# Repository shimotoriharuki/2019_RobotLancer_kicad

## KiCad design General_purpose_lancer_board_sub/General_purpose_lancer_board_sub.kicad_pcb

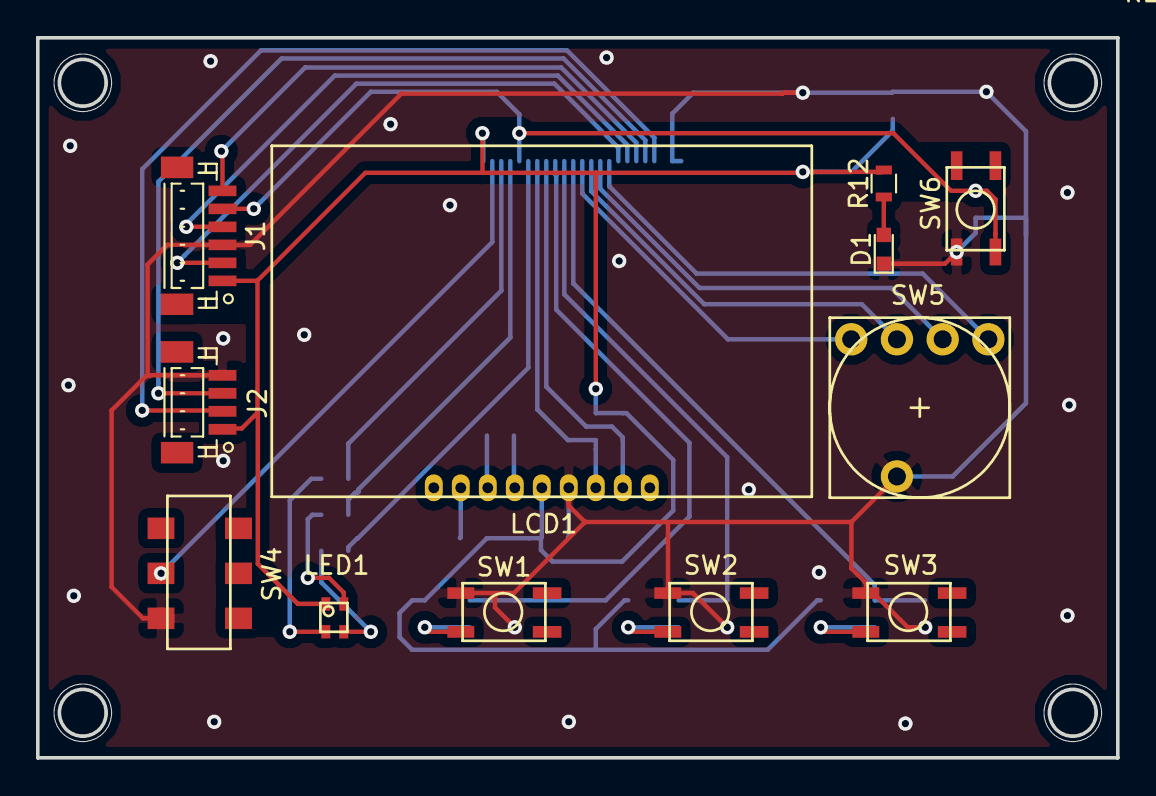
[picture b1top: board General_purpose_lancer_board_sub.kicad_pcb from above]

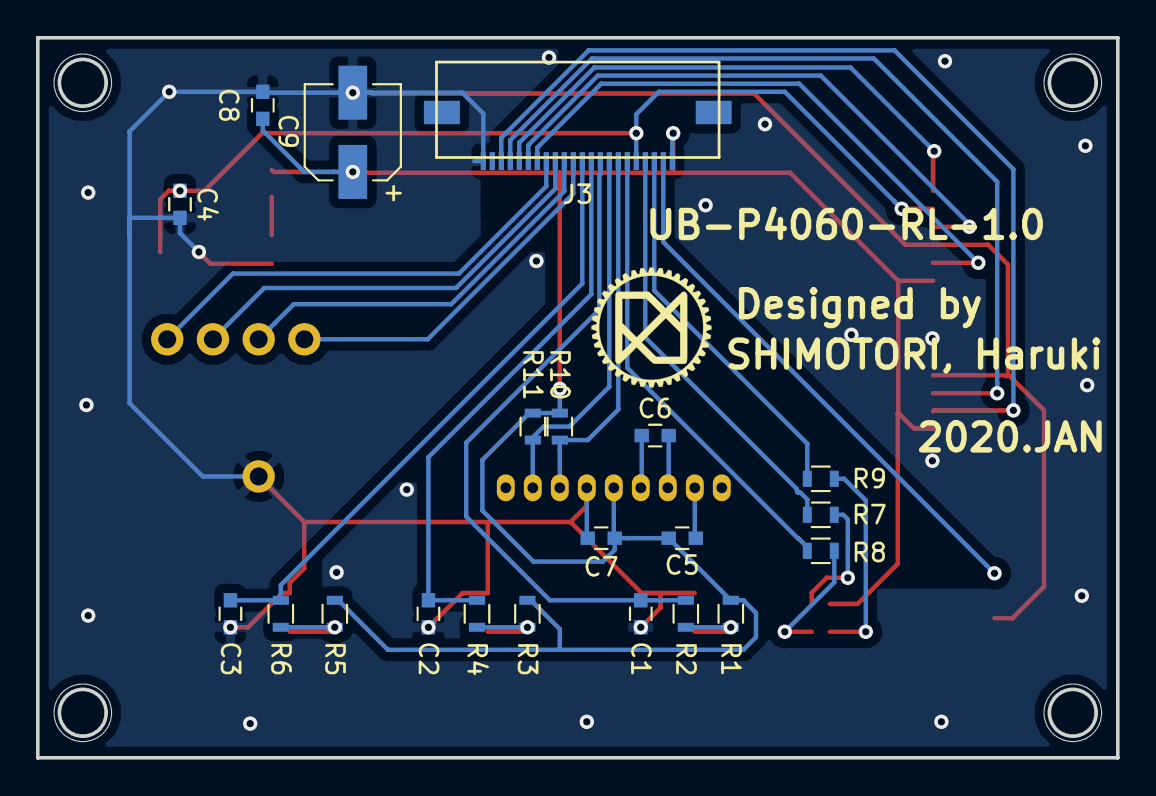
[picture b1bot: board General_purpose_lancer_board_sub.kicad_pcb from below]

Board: 2 copper layers, 60.0 x 40.0 mm, 33 parts (21 on the bottom side), 31 nets.

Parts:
C1, C2, C3, C4, C7: 0.1u; C_0603
C5, C6: 1u; C_0603
C8: 0.1; C_0603
C9: 82u; CP_Elec_5x5.8
D1: LED; LED_0603
J1: SH; JST_SH_BM06B-SRSS-TB_06x1.00mm_Straight
J2: SH; JST_SH_BM04B-SRSS-TB_04x1.00mm_Straight
J3: FFC; Molex_FFC_22
LCD1: AQM0802A
LED1: OSTB0603C1C-A
R1, R2, R3, R4, R5, R6: 10k; R_0603
R7: 1.2k; R_0603
R8: 680; R_0603
R9: 470; R_0603
R10, R11: 4.7k; R_0603
R12: 360; R_0603
SW1, SW2, SW3, SW6: SKRPACE010
SW4: SSSS213202
SW5: FR01SC16P-S; FR01SC16P

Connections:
+3V3: C5.2, C7.2, C8.1, C9.1, J1.1, J2.1, J3.22, LCD1.5, LED1.1, R1.1, R3.1, R5.1, R10.1, R11.1, R12.1
GND: C1.1, C2.1, C3.1, C4.2, C7.1, C8.2, C9.2, D1.1, J1.3, J2.4, J3.1, LCD1.6, SW1.2, SW2.2, SW3.2, SW4.3, SW5.C, SW6.2
I2C_SCL_LCD: J3.15, LCD1.8, R11.2
I2C_SDA_LCD: J3.16, LCD1.7, R10.2
LED2_B: J3.20, R9.1
LED2_G: J3.17, R8.1
LED2_R: J3.19, R7.1
NRST: C4.1, J1.5, J3.18, SW6.1
unnamed: C5.1, LCD1.2
unnamed: C6.1, LCD1.4
unnamed: C6.2, LCD1.3
unnamed: D1.2, R12.2
unnamed: LED1.2, R7.2
unnamed: LED1.3, R9.2
unnamed: LED1.4, R8.2
unnamed: R1.2, R2.2, SW1.1
unnamed: R3.2, R4.2, SW2.1
unnamed: R5.2, R6.2, SW3.1
POWER_SW: J3.21, SW4.2
R_SW1: J3.11, SW5.1
R_SW2: J3.10, SW5.2
R_SW4: J3.9, SW5.4
R_SW8: J3.8, SW5.8
SWCLK: J1.2, J3.7
SWDIO: J1.4, J3.6
SWO: J1.6, J3.5
T_SW1: C1.2, J3.14, R2.1
T_SW2: C2.2, J3.13, R4.1
T_SW3: C3.2, J3.12, R6.1
UART_RX: J2.2, J3.3
UART_TX: J2.3, J3.4

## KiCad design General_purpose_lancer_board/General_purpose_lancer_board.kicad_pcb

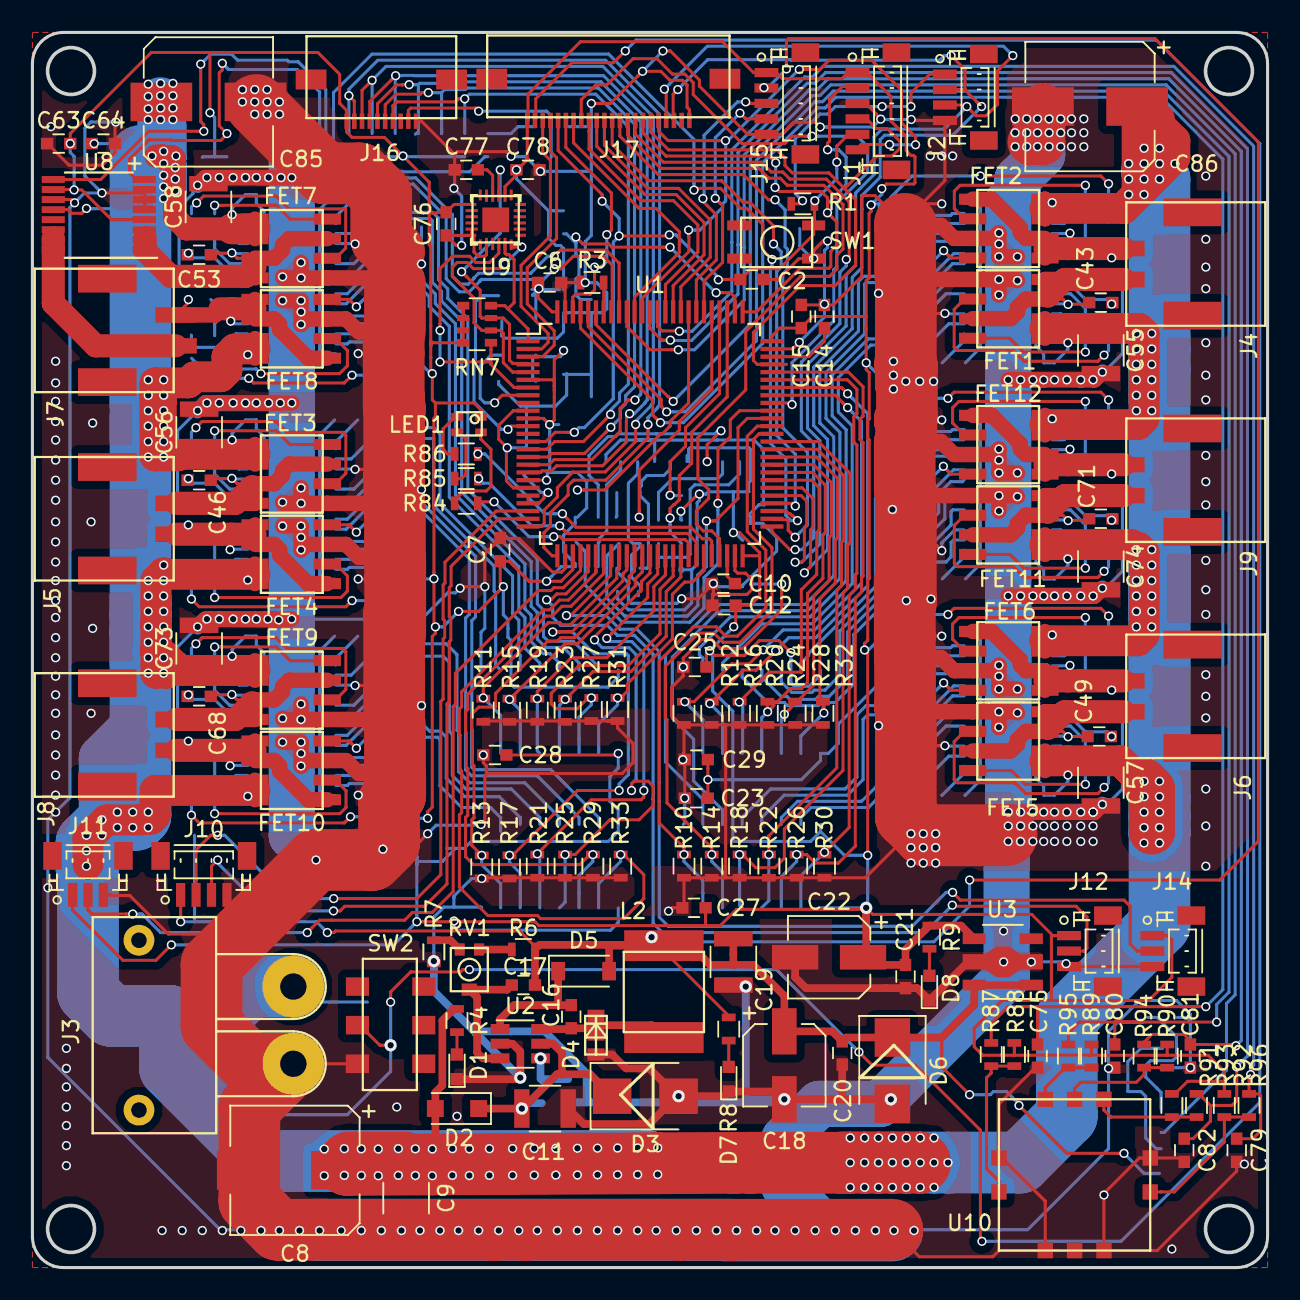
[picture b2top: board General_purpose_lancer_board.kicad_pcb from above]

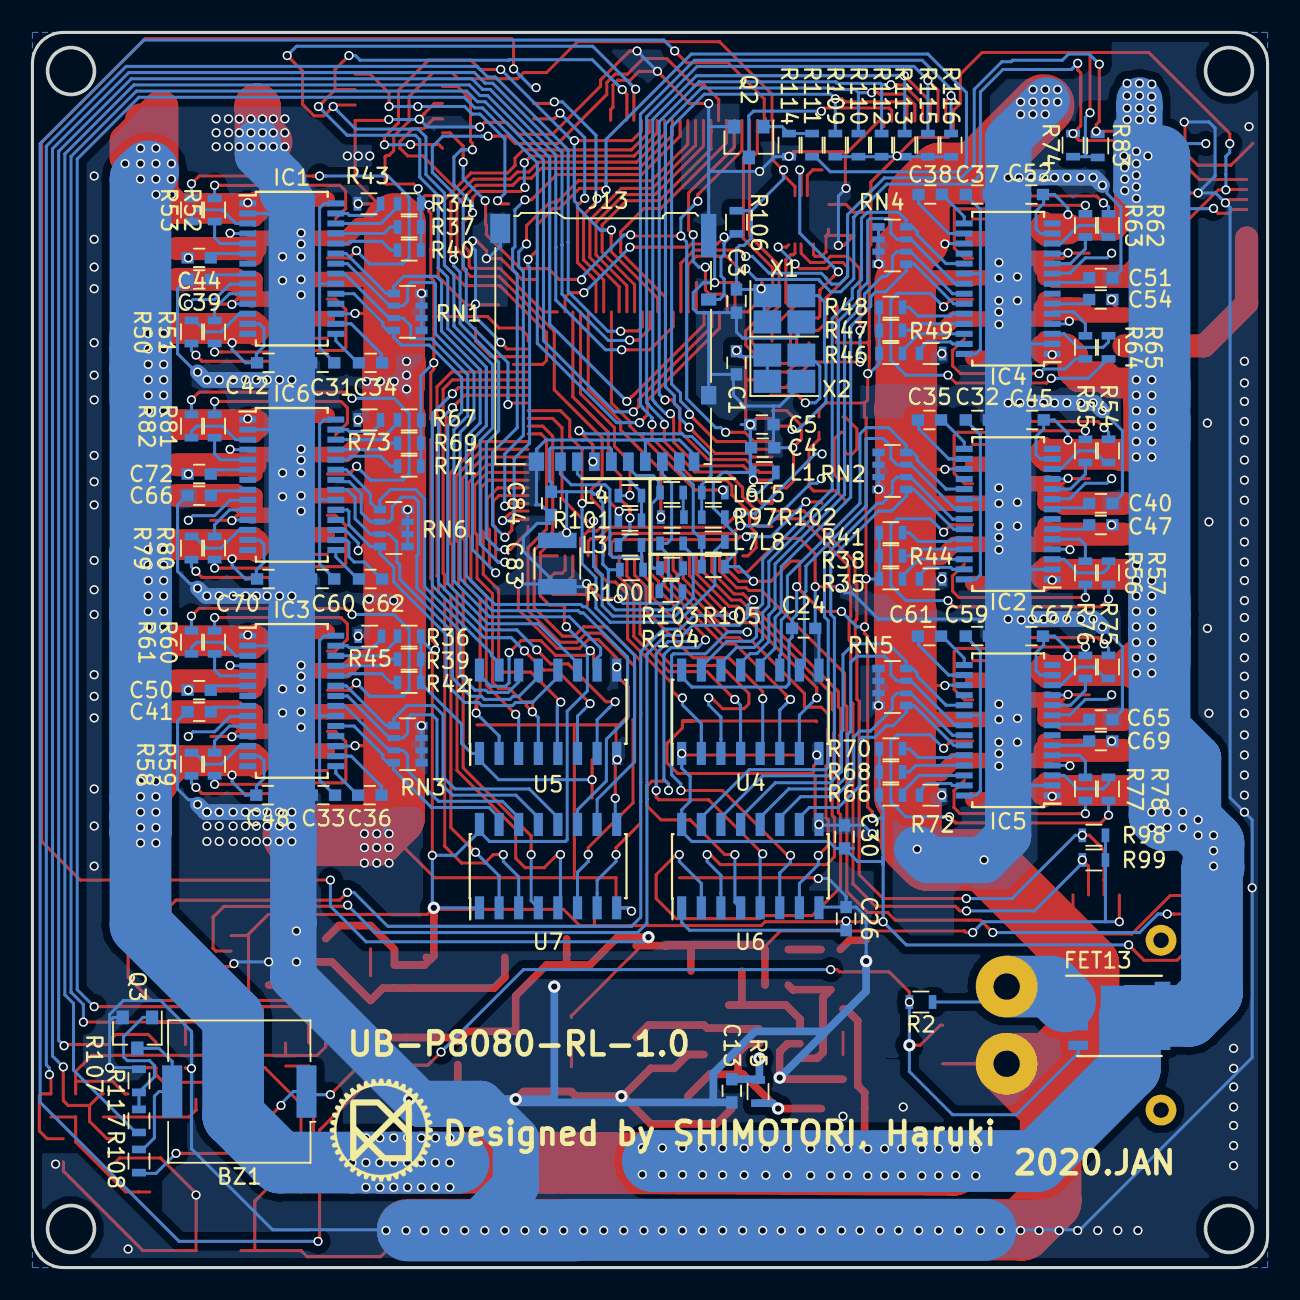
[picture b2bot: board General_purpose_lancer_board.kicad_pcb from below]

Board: 2 copper layers, 80.0 x 80.0 mm, 281 parts (143 on the bottom side), 265 nets.

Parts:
BZ1: PKMCS0909E4000-R1; Buzzer_Murata_PKMCS0909E4000-R1
C1, C2, C3, C4, C5, C6, C7, C12, C13, C15, C23, C24, C25, C26, C27, C28, C29, C30, C31, C32, C33, C37, C59, C60, C63, C64, C76, C77, C78: 0.1u; C_0603
C8, C85, C86: 330u; CP_Elec_8x6.7
C9, C11, C19, C55, C56, C57, C58, C73, C74, C83: 47u; C_1210
C10, C14: 2.2u; C_0603
C16: 0.01u; C_0603
C17: 470p; C_0603
C18, C22: 100u; CP_Elec_5x5.8
C20: 1u; C_0603
C21, C42, C45, C48, C52, C67, C70, C75, C79, C80, C81, C82: 10u; C_0603
C34, C35, C36, C38, C61, C62: 470n; C_0603
C39, C40, C41, C43, C44, C46, C47, C49, C50, C51, C53, C54, C65, C66, C68, C69, C71, C72: 0.22u; C_0603
C84: 0.1; C_0603
D1, D7, D8: OSBL1608; LED_0603
D2: SS2040; D_SOD-123F
D3: 1SMB5930BT3G; D_SMB
D4: RSX101VAM; TUMD2M
D5: 1N4148; D_SOD-123
D6: 1SMB5920BT3G; D_SMB
FET1, FET2, FET3, FET4, FET5, FET6, FET7, FET8, FET9, FET10, FET11, FET12: IRF8915
FET13: SiSS27ADN; SO-8_PowerPAK_Vishay_Single
IC1, IC2, IC3, IC4, IC5, IC6: A3921; TSSOP-28-1EP_4.4x9.7mm_Pitch0.65mm
J1: SH; JST_SH_BM06B-SRSS-TB_06x1.00mm_Straight
J2, J10: SH; JST_SH_BM04B-SRSS-TB_04x1.00mm_Straight
J3: XT30; XT30PW-M
J4, J5, J6, J7, J8, J9: PA_SIDE; SM02B-PASS
J11, J12, J14: SH; JST_SH_BM03B-SRSS-TB_03x1.00mm_Straight
J13: Micro_SD_Card_Det_Hirose_DM3AT; Hirose_DM3AT-SF-PEJM5
J15: SH; JST_SH_BM05B-SRSS-TB_05x1.00mm_Straight
J16: FFC; Molex_FFC_10
J17: FFC; Molex_FFC_22
L1: 330; L_0603
L2: 22u; SD25-220-R
L3, L4, L5, L6, L7, L8: 100; L_0603
LED1: OSTB0603C1C-A
Q2: IRLML6344; SOT-23
Q3: BSS138; SOT-23
R1: 50k; R_0603
R2: 12k; R_0603
R3, R7, R87, R88, R89, R90, R91, R92, R93, R94, R95, R96, R98, R99, R107: 10k; R_0603
R4: 6.8K; R_0603
R5: 15K; R_0603
R6: 30k; R_0603
R8: 1.8K; R_0603
R9: 390; R_0603
R10, R11, R12, R13, R14, R15, R16, R17, R18, R19, R20, R21, R22, R23, R24, R25, R26, R27, R28, R29, R30, R31, R32, R33, R34, R35, R36, R37, R38, R39, R40, R41, R42, R46, R47, R48, R66, R67, R68, R69, R70, R71: 10K; R_0603
R43, R44, R45, R49, R72, R73: 5k; R_0603
R50, R51, R52, R53, R54, R55, R56, R57, R58, R59, R60, R61, R62, R63, R64, R65, R75, R76, R77, R78, R79, R80, R81, R82: 75; R_0603
R74, R83: 4.7k; R_0603
R84: 1.2k; R_0603
R85: 680; R_0603
R86: 470; R_0603
R97: 0; R_0603
R100, R101, R102, R103, R104, R105, R106: 22k; R_0603
R108: 1k; R_0603
R109, R110, R112, R113, R115, R116: R; R_0603
R111, R117: 45; R_0603
R114: 47k; R_0603
RN1, RN2, RN3, RN4, RN5, RN6: 10K; R_Array_Convex_4x0603
RN7: 4.7k; R_Array_Convex_4x0603
RV1: ST2TA101; ST2TA
SW1: SW_Push; SKRPACE010
SW2: SSSS213202
U1: STM32F446VE; LQFP-100_14x14mm_Pitch0.5mm
U2: LT1933; TSOT-23-6
U3: NJM2884U1-33; SOT-89-5_Housing
U4, U5, U6, U7: SI8660BA; SOIC-16_3.9x9.9mm_Pitch1.27mm
U8: INA260; TSSOP-16_4.4x5mm_Pitch0.65mm
U9: ICM20648
U10: JS1300AQ; JS1300
X1: ECS-2520S; Crystal_SMD_EuroQuartz_X22-4pin_2.5x2.0mm_HandSoldering
X2: TC25L5I32K7680; Crystal_SMD_EuroQuartz_X22-4pin_2.5x2.0mm_HandSoldering

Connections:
+3V3: C1.1, C3.1, C4.2, C5.1, C6.2, C7.1, C12.1, C15.1, C21.1, C22.1, C23.1, C24.1, C25.1, C26.1, C27.1, C28.1, C29.1, C30.1, C63.1, C76.1, C78.2, C83.1, C84.1, J1.1, J2.1, J11.1, J12.1, J13.4, J14.1, J15.1, J16.1, J17.1, L1.2, LED1.1, R1.1, R9.1, R34.1, R35.1, R36.1, R37.1, R38.1, R39.1, R40.1, R41.1, R42.1, R46.1, R47.1, R48.1, R66.1, R67.1, R68.1, R69.1, R70.1, R71.1, R74.1, R83.1, R88.1, R89.1, R90.1, R91.1, R92.1, R100.1, R101.1, R102.1, R104.1, R105.1, R106.1, R109.1, R110.1, R112.1, R113.1, R115.1, R116.1, RN7.5, RN7.6, RN7.7, RN7.8, U1.6, U1.11, U1.19, U1.28, U1.50, U1.75, U1.100, U3.4, U4.1, U4.16, U5.1, U5.16, U6.1, U6.16, U7.1, U7.16, U8.4, U8.10, U9.8, U9.13, X1.1, X1.4, X2.1, X2.4
+5V: BZ1.1, C17.1, C18.1, C19.1, C20.1, D5.2, D6.1, J10.1, J15.2, L2.1, R6.1, R8.1, R98.1, R99.1, R108.2, U3.1, U3.5
+BATT: C8.1, C9.1, C42.1, C45.1, C48.1, C52.1, C55.1, C56.1, C57.1, C58.1, C64.1, C67.1, C70.1, C73.1, C74.1, C85.1, C86.1, D2.2, FET1.5, FET1.6, FET2.7, FET2.8, FET3.5, FET3.6, FET4.7, FET4.8, FET5.5, FET5.6, FET6.7, FET6.8, FET7.5, FET7.6, FET8.7, FET8.8, FET9.5, FET9.6, FET10.7, FET10.8, FET11.5, FET11.6, FET12.7, FET12.8, FET13.5, FET13.6, FET13.7, FET13.8, IC1.1, IC1.13, IC2.1, IC2.13, IC3.1, IC3.13, IC4.1, IC4.13, IC5.1, IC5.13, IC6.1, IC6.13, R4.1, U8.12
ADC_LINE1: J16.7, R109.2, U1.15
ADC_LINE2: J16.6, R110.2, U1.16
ADC_LINE3: J16.5, R112.2, U1.17
ADC_LINE4: J16.4, R113.2, U1.18
ADC_LINE5: J16.3, R115.2, U1.25
ADC_LINE6: J16.2, R116.2, U1.26
ADC_POT1: J11.2, U1.29
ADC_POT2: J12.2, U1.30
ADC_POT3: J14.2, U1.33
C_SW1: C82.1, R93.1, U1.88
C_SW2: C81.1, R94.1, U1.91
C_SW3: C80.1, R95.1, U1.96
C_SW4: C79.1, R96.1, U1.87
C_SW5: C75.1, R87.2, U1.97
ENCORDER_A: J10.2, R98.2, U1.23
ENCORDER_B: J10.3, R99.2, U1.24
GND: C1.2, C2.2, C3.2, C4.1, C5.2, C6.1, C7.2, C8.2, C9.2, C10.2, C11.2, C12.2, C13.2, C14.1, C15.2, C18.2, C19.2, C20.2, C21.2, C22.2, C23.2, C24.2, C25.2, C26.2, C27.2, C28.2, C29.2, C30.2, C31.2, C32.2, C33.2, C37.2, C39.2, C40.2, C41.2, C42.2, C45.2, C48.2, C51.2, C52.2, C55.2, C56.2, C57.2, C58.2, C59.2, C60.2, C63.2, C64.2, C65.2, C66.2, C67.2, C70.2, C73.2, C74.2, C75.2, C76.2, C77.1, C78.1, C79.2, C80.2, C81.2, C82.2, C83.2, C84.2, C85.2, C86.2, D1.1, D3.2, D4.2, D6.2, D7.1, D8.1, FET1.1, FET2.3, FET3.1, FET4.3, FET5.1, FET6.3, FET7.1, FET8.3, FET9.1, FET10.3, FET11.1, FET12.3, IC1.2, IC1.17, IC1.29, IC2.2, IC2.17, IC2.29, IC3.2, IC3.17, IC3.29, IC4.2, IC4.17, IC4.29, IC5.2, IC5.17, IC5.29, IC6.2, IC6.17, IC6.29, J1.3, J2.4, J3.2, J10.4, J11.3, J12.3, J13.6, J13.9, J13.11, J14.3, J15.5, J16.10, J17.22, Q2.2, Q3.2, R3.1, R7.2, R10.2, R11.2, R12.2, R13.2, R14.2, R15.2, R16.2, R17.2, R18.2, R19.2, R20.2, R21.2, R22.2, R23.2, R24.2, R25.2, R26.2, R27.2, R28.2, R29.2, R30.2, R31.2, R32.2, R33.2, R43.2, R44.2, R45.2, R49.2, R72.2, R73.2, R103.2, R107.2, R114.2, RN1.1, RN1.2, RN1.3, RN1.4, RN2.1, RN2.2, RN2.3, RN2.4, RN3.1, RN3.2, RN3.3, RN3.4, RN4.1, RN4.2, RN4.3, RN4.4, RN5.1, RN5.2, RN5.3, RN5.4, RN6.1, RN6.2, RN6.3, RN6.4, SW1.2, SW2.3, U1.10, U1.20, U1.27, U1.49, U1.74, U1.99, U2.2, U3.2, U4.8, U4.9, U5.8, U5.9, U6.8, U6.9, U7.8, U7.9, U8.5, U8.6, U8.7, U8.11, U9.17, U9.18, U9.20, U10.1, U10.3, U10.4, U10.5, U10.7, X1.2, X2.2
GPIO_DRIVE1_P: R15.1, U1.37, U4.6
GPIO_DRIVE1_P_I: IC2.19, RN2.8, U4.11
GPIO_DRIVE1_SR: R11.1, U1.34, U4.7
GPIO_DRIVE1_SR_I: IC2.21, RN2.7, U4.10
GPIO_DRIVE2_P: R25.1, U1.38, U6.4
GPIO_DRIVE2_P_I: IC5.19, RN5.8, U6.13
GPIO_DRIVE2_SR: R21.1, U1.39, U6.5
GPIO_DRIVE2_SR_I: IC5.21, RN5.7, U6.12
GPIO_DRIVE3_P: R20.1, U1.57, U5.5
GPIO_DRIVE3_P_I: IC6.19, RN6.8, U5.12
GPIO_DRIVE3_SR: R24.1, U1.58, U5.4
GPIO_DRIVE3_SR_I: IC6.21, RN6.7, U5.13
GPIO_DRIVE4_P: R30.1, U1.70, U7.2
GPIO_DRIVE4_P_I: IC3.19, RN3.8, U7.15
GPIO_DRIVE4_SR: R26.1, U1.71, U7.3
GPIO_DRIVE4_SR_I: IC3.21, RN3.7, U7.14
GPIO_SERVO1_SR: R27.1, U1.41, U4.3
GPIO_SERVO1_SR_I: IC4.21, RN4.7, U4.14
GPIO_SERVO2_SR: R12.1, U1.68, U5.7
GPIO_SERVO2_SR_I: IC1.21, RN1.7, U5.10
I2C_SCL_CURRENT: R83.2, U1.92, U8.9
I2C_SCL_LCD: J17.8, U1.67
I2C_SDA_CURRENT: R74.2, U1.93, U8.8
I2C_SDA_LCD: J17.7, U1.90
LED1_B: R86.1, U1.46
LED1_G: R85.1, U1.44
LED1_R: R84.1, U1.43
LED2_B: J17.3, U1.2
LED2_G: J17.6, U1.98
LED2_R: J17.4, U1.3
NRST: C2.1, J1.5, J17.5, R1.2, SW1.1, U1.14
unnamed: BZ1.2, Q3.3, R108.1
unnamed: C10.1, U1.48
unnamed: C11.1, D2.1, D3.1, R5.1, U2.5
unnamed: C13.1, R5.2, U2.4
unnamed: C14.2, U1.73
unnamed: C16.1, D5.1, U2.1
unnamed: C16.2, D4.1, L2.2, U2.6
unnamed: C17.2, RV1.2, U2.3
unnamed: C31.1, IC1.20, IC1.28
unnamed: C32.1, IC2.20, IC2.28
unnamed: C33.1, IC3.20, IC3.28
unnamed: C34.1, IC1.16
unnamed: C34.2, IC1.15
unnamed: C35.1, IC2.16
unnamed: C35.2, IC2.15
unnamed: C36.1, IC3.16
unnamed: C36.2, IC3.15
unnamed: C37.1, IC4.20, IC4.28
unnamed: C38.1, IC4.16
unnamed: C38.2, IC4.15
unnamed: C39.1, IC1.8
unnamed: C40.1, IC2.8
unnamed: C41.1, IC3.8
unnamed: C43.1, IC1.9
unnamed: C43.2, FET1.3, FET1.7, FET1.8, IC1.11, J4.1
unnamed: C44.1, IC1.6
unnamed: C44.2, FET2.1, FET2.5, FET2.6, IC1.4, J4.2
unnamed: C46.1, IC2.9
unnamed: C46.2, FET3.3, FET3.7, FET3.8, IC2.11, J5.1
unnamed: C47.1, IC2.6
unnamed: C47.2, FET4.1, FET4.5, FET4.6, IC2.4, J5.2
unnamed: C49.1, IC3.9
unnamed: C49.2, FET5.3, FET5.7, FET5.8, IC3.11, J6.1
unnamed: C50.1, IC3.6
unnamed: C50.2, FET6.1, FET6.5, FET6.6, IC3.4, J6.2
unnamed: C51.1, IC4.8
unnamed: C53.1, IC4.9
unnamed: C53.2, FET7.3, FET7.7, FET7.8, IC4.11, U8.1, U8.2, U8.3
unnamed: C54.1, IC4.6
unnamed: C54.2, FET8.1, FET8.5, FET8.6, IC4.4, J7.1
unnamed: C59.1, IC5.20, IC5.28
unnamed: C60.1, IC6.20, IC6.28
unnamed: C61.1, IC5.16
unnamed: C61.2, IC5.15
unnamed: C62.1, IC6.16
unnamed: C62.2, IC6.15
unnamed: C65.1, IC5.8
unnamed: C66.1, IC6.8
unnamed: C68.1, IC5.9
unnamed: C68.2, FET9.3, FET9.7, FET9.8, IC5.11, J8.1
unnamed: C69.1, IC5.6
unnamed: C69.2, FET10.1, FET10.5, FET10.6, IC5.4, J8.2
unnamed: C71.1, IC6.9
unnamed: C71.2, FET11.3, FET11.7, FET11.8, IC6.11, J9.1
unnamed: C72.1, IC6.6
unnamed: C72.2, FET12.1, FET12.5, FET12.6, IC6.4, J9.2
unnamed: C77.2, U9.10
unnamed: D1.2, R4.2
unnamed: D7.2, R8.2
unnamed: D8.2, R9.2
unnamed: FET1.2, R50.2
unnamed: FET1.4, R51.2
unnamed: FET2.2, R52.2
unnamed: FET2.4, R53.2
unnamed: FET3.2, R54.2
unnamed: FET3.4, R55.2
unnamed: FET4.2, R56.2
unnamed: FET4.4, R57.2
unnamed: FET5.2, R58.2
unnamed: FET5.4, R59.2
unnamed: FET6.2, R60.2
unnamed: FET6.4, R61.2
unnamed: FET7.2, R62.2
unnamed: FET7.4, R63.2
unnamed: FET8.2, R64.2
unnamed: FET8.4, R65.2
unnamed: FET9.2, R75.2
unnamed: FET9.4, R76.2
unnamed: FET10.2, R77.2
unnamed: FET10.4, R78.2
unnamed: FET11.2, R79.2
unnamed: FET11.4, R80.2
unnamed: FET12.2, R81.2
unnamed: FET12.4, R82.2
unnamed: FET13.1, FET13.2, FET13.3, J3.1, R2.1
unnamed: IC1.3, R53.1
unnamed: IC1.5, R52.1
unnamed: IC1.10, R51.1
unnamed: IC1.12, R50.1
unnamed: IC1.24, R40.2
unnamed: IC1.25, R37.2
unnamed: IC1.26, R34.2
unnamed: IC1.27, R43.1
unnamed: IC2.3, R57.1
unnamed: IC2.5, R56.1
unnamed: IC2.10, R55.1
unnamed: IC2.12, R54.1
unnamed: IC2.24, R41.2
unnamed: IC2.25, R38.2
unnamed: IC2.26, R35.2
unnamed: IC2.27, R44.1
unnamed: IC3.3, R61.1
unnamed: IC3.5, R60.1
unnamed: IC3.10, R59.1
unnamed: IC3.12, R58.1
unnamed: IC3.24, R42.2
unnamed: IC3.25, R39.2
unnamed: IC3.26, R36.2
unnamed: IC3.27, R45.1
unnamed: IC4.3, R65.1
unnamed: IC4.5, R64.1
unnamed: IC4.10, R63.1
unnamed: IC4.12, R62.1
unnamed: IC4.24, R48.2
unnamed: IC4.25, R47.2
unnamed: IC4.26, R46.2
unnamed: IC4.27, R49.1
unnamed: IC5.3, R78.1
unnamed: IC5.5, R77.1
unnamed: IC5.10, R76.1
unnamed: IC5.12, R75.1
unnamed: IC5.24, R70.2
unnamed: IC5.25, R68.2
unnamed: IC5.26, R66.2
unnamed: IC5.27, R72.1
unnamed: IC6.3, R82.1
unnamed: IC6.5, R81.1
unnamed: IC6.10, R80.1
unnamed: IC6.12, R79.1
unnamed: IC6.24, R71.2
unnamed: IC6.25, R69.2
unnamed: IC6.26, R67.2
unnamed: IC6.27, R73.1
unnamed: J7.2, U8.14, U8.15, U8.16
unnamed: J13.1, L3.1, R100.2
unnamed: J13.2, L4.1, R101.2
unnamed: J13.3, L5.1, R102.2
unnamed: J13.5, L6.1, R103.1
unnamed: J13.7, L7.1, R104.2
unnamed: J13.8, L8.1, R105.2
unnamed: J16.9, Q2.3
unnamed: L1.1, U1.21, U1.22
unnamed: L6.2, R97.1
unnamed: LED1.2, R84.2
unnamed: LED1.3, R86.2
unnamed: LED1.4, R85.2
unnamed: Q2.1, R111.1, R114.1
unnamed: Q3.1, R107.1, R117.1
unnamed: R3.2, U1.94
unnamed: R6.2, RV1.3
unnamed: R7.1, RV1.1
unnamed: R87.1, R88.2, U10.2
unnamed: R89.2, R95.2, U10.10
unnamed: R90.2, R94.2, U10.9
unnamed: R91.2, R93.2, U10.8
unnamed: R92.2, R96.2, U10.6
OSC32_IN: U1.8, X2.3
OSC_IN: U1.12, X1.3
POWER_SW: FET13.4, J17.2, R2.2, SW2.2
PWM_BZ: R117.2, U1.95
PWM_DRIVE1_H: R29.1, U1.32, U6.3
PWM_DRIVE1_H_I: IC2.23, RN2.5, U6.14
PWM_DRIVE1_L: R33.1, U1.31, U6.2
PWM_DRIVE1_L_I: IC2.22, RN2.6, U6.15
PWM_DRIVE2_H: R13.1, U1.36, U6.7
PWM_DRIVE2_H_I: IC5.23, RN5.5, U6.10
PWM_DRIVE2_L: R17.1, U1.35, U6.6
PWM_DRIVE2_L_I: IC5.22, RN5.6, U6.11
PWM_DRIVE3_H: R32.1, U1.60, U5.2
PWM_DRIVE3_H_I: IC6.23, RN6.5, U5.15
PWM_DRIVE3_L: R28.1, U1.59, U5.3
PWM_DRIVE3_L_I: IC6.22, RN6.6, U5.14
PWM_DRIVE4_H: R18.1, U1.62, U7.5
PWM_DRIVE4_H_I: IC3.23, RN3.5, U7.12
PWM_DRIVE4_L: R22.1, U1.61, U7.4
PWM_DRIVE4_L_I: IC3.22, RN3.6, U7.13
PWM_LINE_SENSOR: R111.2, U1.53
PWM_SERVO1_H: R19.1, U1.40, U4.5
PWM_SERVO1_H_I: IC4.23, RN4.5, U4.12
PWM_SERVO1_L: R23.1, U1.42, U4.4
PWM_SERVO1_L_I: IC4.22, RN4.6, U4.13
PWM_SERVO1_P: R31.1, U1.45, U4.2
PWM_SERVO1_P_I: IC4.19, RN4.8, U4.15
PWM_SERVO2_H: R10.1, U1.64, U7.7
PWM_SERVO2_H_I: IC1.23, RN1.5, U7.10
PWM_SERVO2_L: R14.1, U1.63, U7.6
PWM_SERVO2_L_I: IC1.22, RN1.6, U7.11
PWM_SERVO2_P: R16.1, U1.69, U5.6
PWM_SERVO2_P_I: IC1.19, RN1.8, U5.11
REMAINDER_PD0: J15.4, U1.81
REMAINDER_PD1: J15.3, U1.82
R_SW1: J17.12, U1.54
R_SW2: J17.13, U1.52
R_SW4: J17.14, U1.47
R_SW8: J17.15, U1.51
SDIO_CK: R97.2, U1.80
SDIO_CMD: L5.2, U1.83
SDIO_D0: L7.2, U1.65
SDIO_D1: L8.2, U1.66
SDIO_D2: L3.2, U1.78
SDIO_D3: L4.2, U1.79
SD_INSERT: J13.10, R106.2, U1.77
SPI_CS_IMU: RN7.1, U1.7, U9.22
SPI_MISO_IMU: RN7.3, U1.4, U9.9
SPI_MOSI_IMU: RN7.2, U1.5, U9.24
SPI_SCK_IMU: RN7.4, U1.1, U9.23
SWCLK: J1.2, J17.16, U1.76
SWDIO: J1.4, J17.17, U1.72
SWO: J1.6, J17.18, U1.89
T_SW1: J17.9, U1.86
T_SW2: J17.10, U1.85
T_SW3: J17.11, U1.84
USART_RX: J2.2, J17.20, U1.56
USART_TX: J2.3, J17.19, U1.55

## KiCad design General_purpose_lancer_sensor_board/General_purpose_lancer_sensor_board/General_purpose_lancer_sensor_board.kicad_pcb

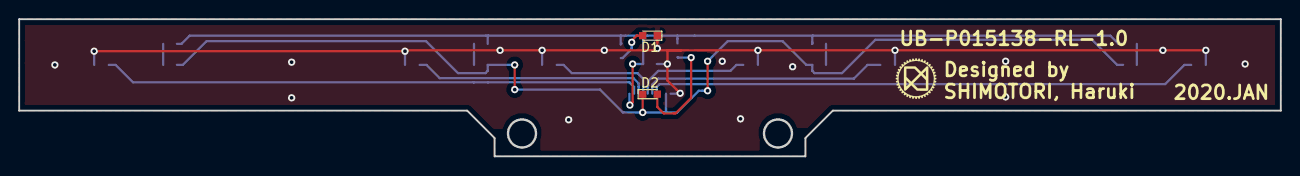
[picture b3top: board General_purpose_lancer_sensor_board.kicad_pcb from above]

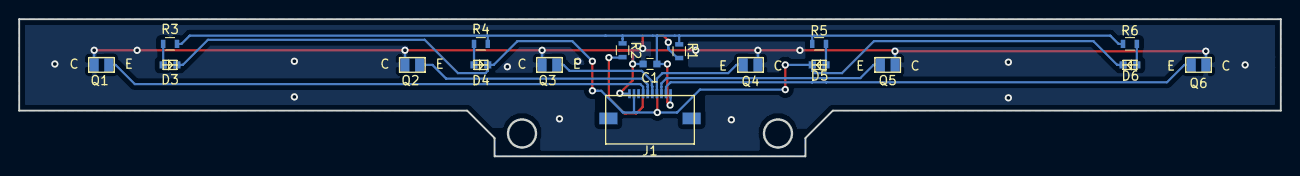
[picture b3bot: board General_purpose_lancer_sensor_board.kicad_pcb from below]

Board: 2 copper layers, 138.0 x 15.0 mm, 20 parts (18 on the bottom side), 15 nets.

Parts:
C1: 1u; C_0603
D1, D2: LED; LED_0603
D3, D4, D5, D6: SIR19-21C
J1: FFC; Molex_FFC_10
Q1, Q2, Q3, Q4, Q5, Q6: TEMT7100X01
R1, R2: 330; R_0603
R3, R4, R5, R6: 100; R_0603

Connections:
+3V3: C1.1, J1.1, R1.1, R2.1, R3.1, R4.1, R5.1, R6.1
ADC_LINE1: J1.7, Q1.1
ADC_LINE2: J1.6, Q2.1
ADC_LINE3: J1.5, Q3.1
ADC_LINE4: J1.4, Q4.1
ADC_LINE5: J1.3, Q5.1
ADC_LINE6: J1.2, Q6.1
GND: C1.2, D1.1, J1.10, Q1.2, Q2.2, Q3.2, Q4.2, Q5.2, Q6.2
unnamed: D1.2, R1.2
unnamed: D2.2, R2.2
unnamed: D3.2, R3.2
unnamed: D4.2, R4.2
unnamed: D5.2, R5.2
unnamed: D6.2, R6.2
PULS: D2.1, D3.1, D4.1, D5.1, D6.1, J1.9

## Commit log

2021-03-22 init
2021-03-22 Create LICENSE
2022-09-22 ファイル整理
